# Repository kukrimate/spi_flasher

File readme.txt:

This project contains a schematic and board design for a breakout board for
the Microchip MCP2210 with a pin header to connect an SPI flash device.

Both files are in the file format of EAGLE from Autodesk.

Assembly suggestions: Use a very fine tipped soldering iron set to 300-350 C,
use very small diameter rosin core solder wire and DO use extra flux.

In the `pictures` directory you can see some high resolution pictures taken
of a device built (hand-soldered) using this design.

For software, for now you can use my modified version of flashrom. Hopefully
support for this will be upstreamed soon.
It supports both libusb (mcp2210_libusb branch) and directly using the hidraw
kernel interface on Linux.
https://github.com/kukrimate/flashrom

==== COPYING ====

Any person obtaining a copy of this schematic and board design is permitted to
use, modify and/or distribute this schematic and board design for any purpose,
including, but not limited to commercial use with the only requirement
of not removing the copyright notice from the board silkscreen.

==== IMPORTANT DISCLAIMER ====

THE SCHEMATIC AND BOARD DESIGN IS PROVIDED "AS IS"
AND THE AUTHOR DISCLAIMS ALL WARRANTIES WITH REGARD TO THIS
SCHEMATIC AND BOARD DESIGN INCLUDING ALL IMPLIED WARRANTIES OF
MERCHANTABILITY AND FITNESS. IN NO EVENT SHALL THE AUTHOR BE LIABLE FOR
ANY SPECIAL, DIRECT, INDIRECT, OR CONSEQUENTIAL DAMAGES OR ANY DAMAGES
WHATSOEVER RESULTING FROM LOSS OF USE, DATA OR PROFITS, WHETHER IN AN
ACTION OF CONTRACT, NEGLIGENCE OR OTHER TORTIOUS ACTION, ARISING OUT OF
OR IN CONNECTION WITH THE USE OR PERFORMANCE OF THE SCHEMATIC AND/OR BOARD
DESIGN OR ANY DEVICE BUILT OR MANUFACTURED FROM THEM.

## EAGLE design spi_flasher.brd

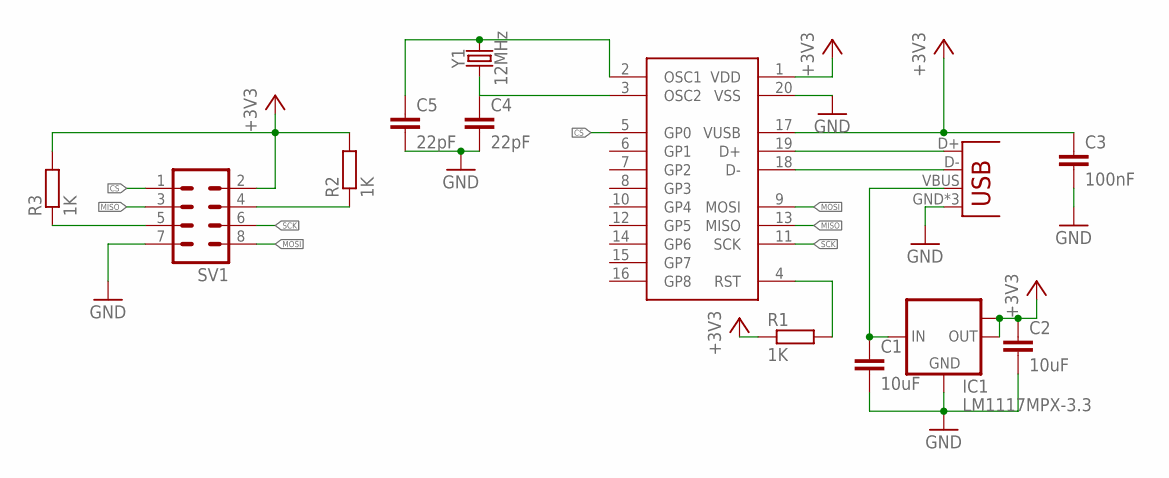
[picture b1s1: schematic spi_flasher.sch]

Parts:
C1, C2: 10uF; C1206
C3: 100nF; C0603
C4, C5: 22pF; C0603
IC1: LM1117MPX-3.3; SOT223
R1, R2, R3: 1K; R0603
SV1: MA04-2
U$1: MCP2210-I/SO; SO20L
X1: USBPTH; USB-B-PTH
Y1: 12MHz; CRYSTAL-SMD-3.2X2.5MM

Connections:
+3V3: C2.1, C3.1, IC1.2 (OUT), IC1.TAB (OUT1), R1.1, R2.2, R3.2, SV1.2, U$1.1 (VDD), U$1.17 (VUSB)
CS: SV1.1, U$1.5 (GP0)
GND: C1.2, C2.2, C3.2, C4.2, C5.2, IC1.1 (GND), SV1.7, U$1.20 (VSS), X1.GND, X1.P$1 (GND), X1.P$2 (GND)
MISO: SV1.3, U$1.13 (MISO)
MOSI: SV1.8, U$1.9 (MOSI)
unnamed: U$1.19 (D+), X1.D+
unnamed: U$1.18 (D-), X1.D-
unnamed: C4.1, U$1.3 (OSC2), Y1.1
unnamed: C1.1, IC1.3 (IN), X1.VBUS
unnamed: C5.1, U$1.2 (OSC1), Y1.3 (2)
unnamed: R1.2, U$1.4 (RST)
unnamed: R3.1, SV1.5
unnamed: R2.1, SV1.4
SCK: SV1.6, U$1.11 (SCK)

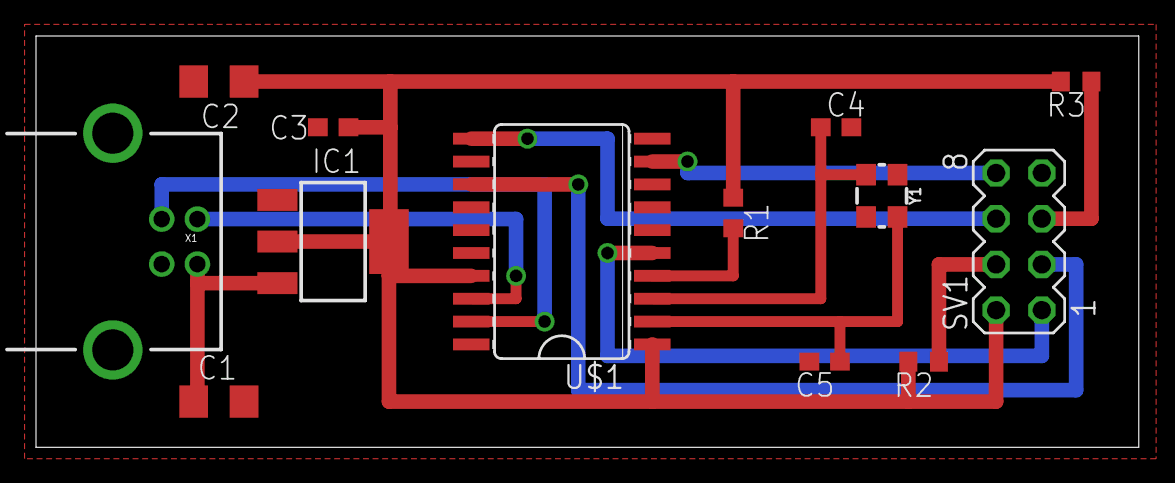
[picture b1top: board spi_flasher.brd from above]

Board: 2 copper layers, 61.3 x 22.9 mm, 13 parts (0 on the bottom side), 14 nets.

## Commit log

2018-12-26 Added a note about software.

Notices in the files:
spi_flasher.brd:
(c) 2018, Máté Kukri
parts and their libraries:
SparkFun-Clocks: Licensing: Creative Commons ShareAlike 4.0 International - https://creativecommons.org/licenses/by-sa/4.0
